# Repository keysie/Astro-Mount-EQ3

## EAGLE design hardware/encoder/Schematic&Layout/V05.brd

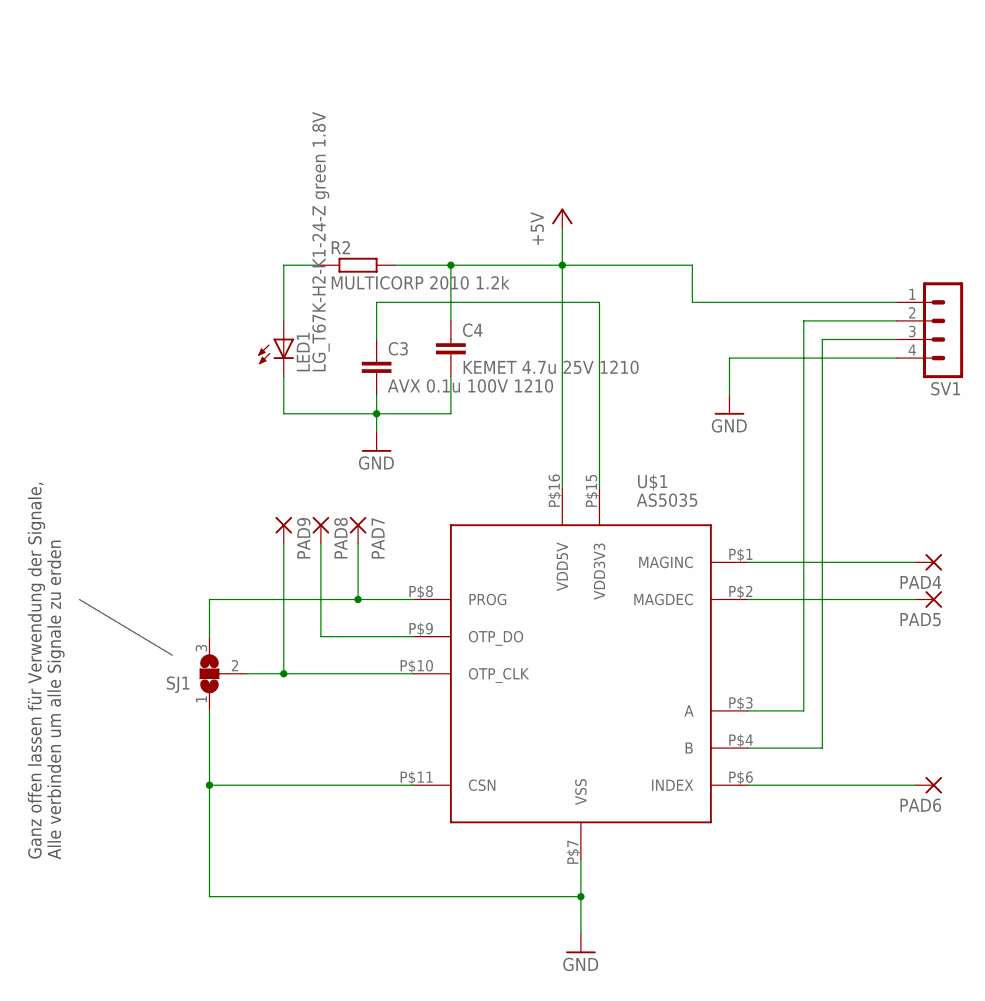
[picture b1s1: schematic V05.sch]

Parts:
C3: AVX 0.1u 100V 1210; C1210
C4: KEMET 4.7u 25V 1210; C1210
LED1: LG_T67K-H2-K1-24-Z green 1.8V; PLCC2
PAD4, PAD5, PAD6, PAD7, PAD8, PAD9: 1,6/0,8
R2: MULTICORP 2010 1.2k; R2010
SJ1: SJ2W; SJ_2
SV1: MA04-1
U$1: AS5035; TSSOP-16

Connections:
+5V: C4.1, R2.2, SV1.1, U$1.P$16 (VDD5V)
GND: C3.2, C4.2, LED1.C, SJ1.1, SV1.4, U$1.P$7 (VSS), U$1.P$11 (CSN)
unnamed: C3.1, U$1.P$15 (VDD3V3)
unnamed: PAD4.1, U$1.P$1 (MAGINC)
unnamed: PAD5.1, U$1.P$2 (MAGDEC)
unnamed: PAD6.1, U$1.P$6 (INDEX)
unnamed: PAD9.1, SJ1.2, U$1.P$10 (OTP_CLK)
unnamed: LED1.A, R2.1
unnamed: SV1.3, U$1.P$4 (B)
unnamed: SV1.2, U$1.P$3 (A)
unnamed: PAD7.1, SJ1.3, U$1.P$8 (PROG)
unnamed: PAD8.1, U$1.P$9 (OTP_DO)

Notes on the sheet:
Ganz offen lassen für Verwendung der Signale, Alle verbinden um alle Signale zu erden

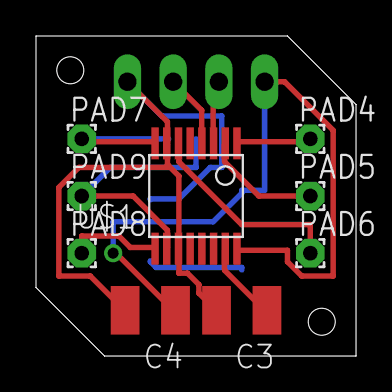
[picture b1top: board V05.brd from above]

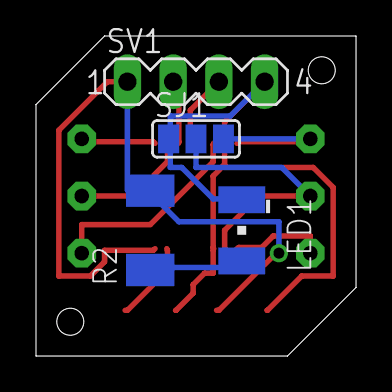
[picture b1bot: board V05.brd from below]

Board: 2 copper layers, 17.8 x 17.8 mm, 13 parts (4 on the bottom side), 12 nets.

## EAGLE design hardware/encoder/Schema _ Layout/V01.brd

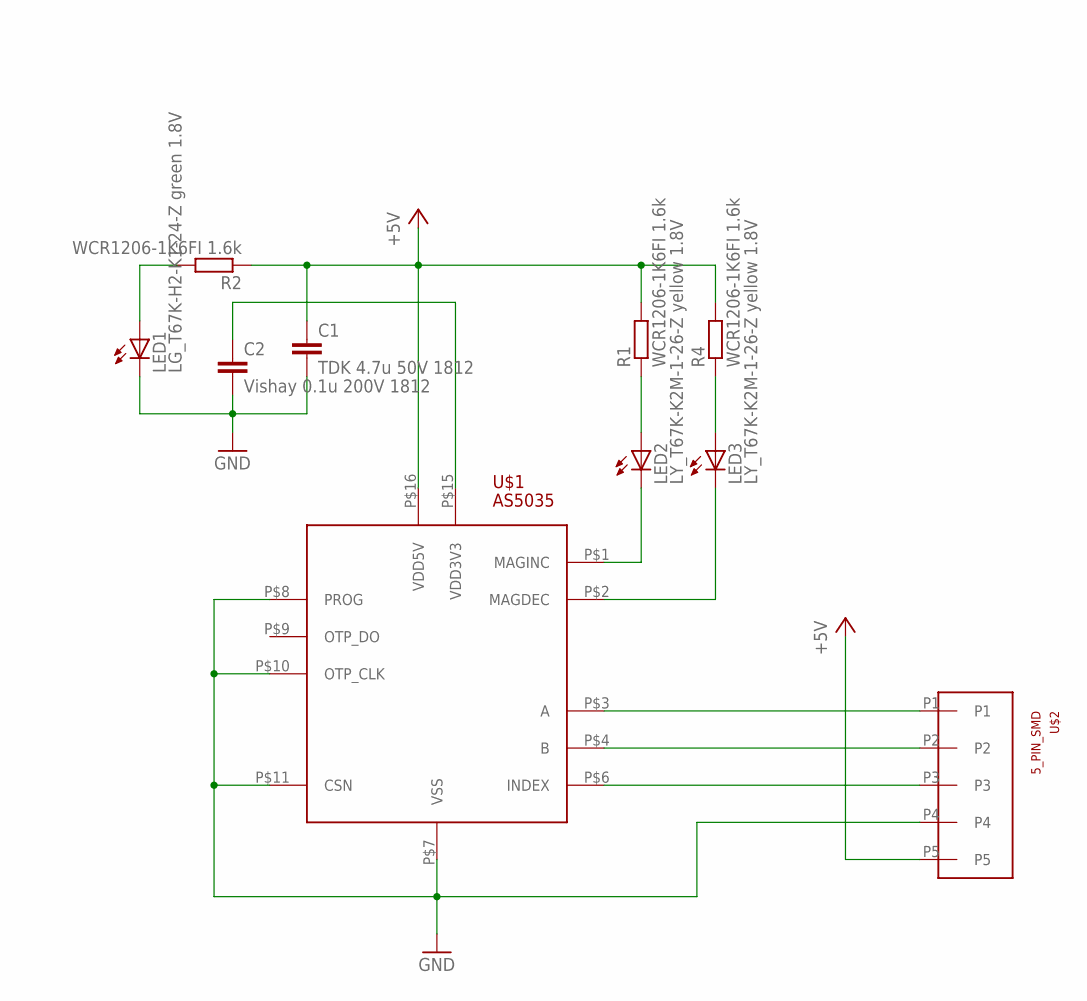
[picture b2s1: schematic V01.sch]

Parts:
C1: TDK 4.7u 50V 1812; C1812K
C2: Vishay 0.1u 200V 1812; C1812K
LED1: LG_T67K-H2-K1-24-Z green 1.8V; PLCC2
LED2, LED3: LY_T67K-K2M-1-26-Z yellow 1.8V; PLCC2
R1, R2, R4: WCR1206-1K6FI 1.6k; R1206
U$1: AS5035; TSSOP-16
U$2: 5_PIN_SMD

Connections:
+5V: C1.1, R1.2, R2.1, R4.2, U$1.P$16 (VDD5V), U$2.P5
GND: C1.2, C2.2, LED1.C, U$1.P$7 (VSS), U$1.P$8 (PROG), U$1.P$10 (OTP_CLK), U$1.P$11 (CSN), U$2.P4
unnamed: C2.1, U$1.P$15 (VDD3V3)
unnamed: LED2.A, R1.1
unnamed: LED2.C, U$1.P$1 (MAGINC)
unnamed: LED3.C, U$1.P$2 (MAGDEC)
unnamed: LED3.A, R4.1
unnamed: LED1.A, R2.2
unnamed: U$1.P$4 (B), U$2.P2
unnamed: U$1.P$3 (A), U$2.P1
unnamed: U$1.P$6 (INDEX), U$2.P3

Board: 2 copper layers, 10 parts (0 on the bottom side), 11 nets, no tracks yet.

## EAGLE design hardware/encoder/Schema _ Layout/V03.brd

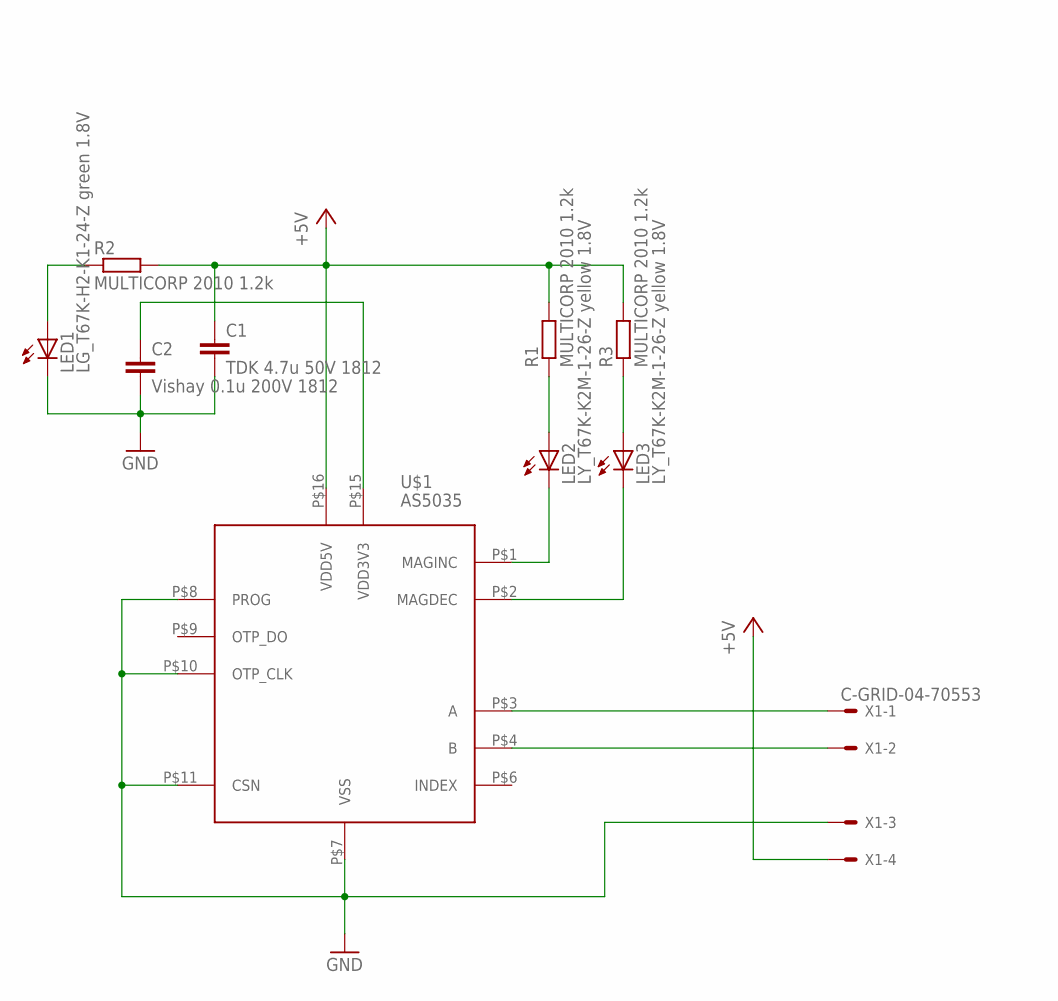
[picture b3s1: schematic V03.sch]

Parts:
C1: TDK 4.7u 50V 1812; C1812K
C2: Vishay 0.1u 200V 1812; C1812K
LED1: LG_T67K-H2-K1-24-Z green 1.8V; PLCC2
LED2, LED3: LY_T67K-K2M-1-26-Z yellow 1.8V; PLCC2
R1, R2, R3: MULTICORP 2010 1.2k; R2010
U$1: AS5035; TSSOP-16
X1: C-GRID-04-70553; 70553-04

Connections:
+5V: C1.1, R1.2, R2.2, R3.2, U$1.P$16 (VDD5V), X1.4
GND: C1.2, C2.2, LED1.C, U$1.P$7 (VSS), U$1.P$8 (PROG), U$1.P$10 (OTP_CLK), U$1.P$11 (CSN), X1.3
unnamed: C2.1, U$1.P$15 (VDD3V3)
unnamed: LED2.A, R1.1
unnamed: LED2.C, U$1.P$1 (MAGINC)
unnamed: LED3.C, U$1.P$2 (MAGDEC)
unnamed: LED3.A, R3.1
unnamed: LED1.A, R2.1
unnamed: U$1.P$4 (B), X1.2
unnamed: U$1.P$3 (A), X1.1

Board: 2 copper layers, 10 parts (1 on the bottom side), 10 nets, no tracks yet.

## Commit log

2016-04-06 Most basic version
    No feedback, Stepper, internal arduino timing source
    No undervoltage protection
2016-04-06 Rename v01_Stativ_no_Encoder_no_Bat.ino to main.ino
2016-04-07 v0.1a: stepper, no feedback, internal clock
2016-04-07 v0.1b: stepper now always powered on
2016-04-07 v0.1c: stepper sleeping again, ext clock
    external clock source used with PIC and 50ppm quarz oscillator. Connected to arduino via an interrupt on change pin.
2016-04-07 v0.1d: encoder feedback
    256-tick magnetic encoder is mounted to measure the rotation of the worm axis. It returns a grey-encoded two-wire signal.
2016-04-07 v0.2a: exchanged stepper with dc-motor, PI control
    Even the smallest possible stepping of the stepper-motor is still to big for astrophotography, because there is no gear in between the motor and the worm-axis. Therefore replaced by dc motor with a g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
    Arduino now outputs a steady stream of controller info such as desired vs measured position etc. on serial on 115200 baud.
2016-04-07 added description to mount.ino
2016-04-08 Matlab Simulink model for controller design
2016-04-09 Additional documentation added
2016-04-09 Documentation folder created
2016-04-09 Hardware setup sketch added
2016-04-09 Added details of gear ratios
2016-04-09 Added aditional hardware info
2016-04-09 even more hardware info
2016-04-09 images compressed
2016-04-09 some more docu added
2016-04-09 angular velocity documentation added
2016-04-10 compressed cad and old schematic data of encoder to conserve space
2016-04-10 folder renamed
2016-04-10 v0.2b: DC/DC-converter-support added
2016-04-10 added hardware docu for version v0.2b (dc/dc-module) as well as docu on external quarz clock which is used since version 0.1c
2016-04-10 Crystal clock board code added
2016-04-10 v0.2c: Encoder and magnet now placed on transmission gear to increase resolution. Also added camer power supply board.
2016-04-10 v0.2c hardware docu updated
2016-04-10 v0.3: I2C-linkup, timing fixed
2016-04-10 v0.3 hardware docu updated
2016-04-10 various test-sketches and matlab script for timer calculation on PIC added
2016-04-10 restructured to comply with arduino studio sketchbook
2016-04-10 README added
2016-04-11 Readme updated
